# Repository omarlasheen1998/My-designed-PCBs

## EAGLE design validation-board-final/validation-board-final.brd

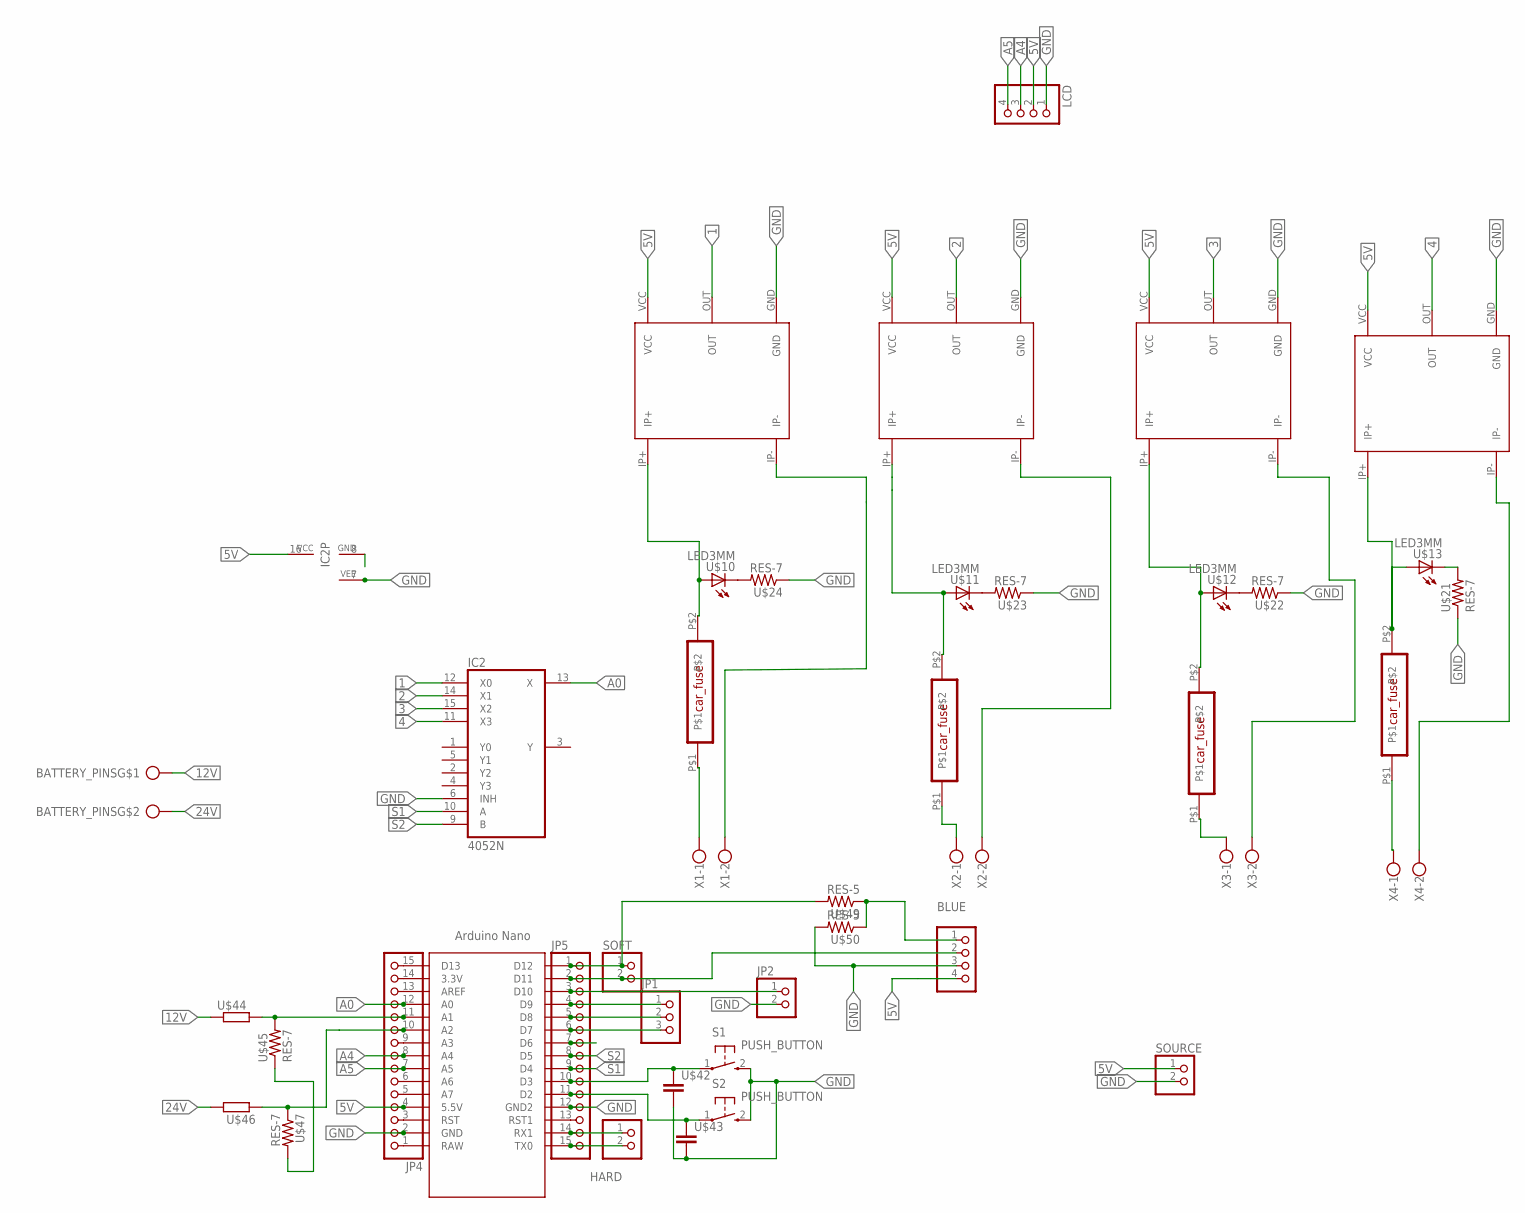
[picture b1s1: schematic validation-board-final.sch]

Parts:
BATTERY_PINS: CON_PTR_2; AK300/2
BLUE: PINHD-4_DATA; 1X04_DATA
HARD: PINHD-2_DATA; 1X02_DATA
IC2: 4052N; DIL16
JP1: PINHD-3_DATA; 1X03_DATA
JP2: PINHD-2_DATA; 1X02_DATA
JP4, JP5: PINHD-1X15; 1X15
LCD: PINHD-4_DATA; 1X04_DATA
S1, S2: PUSH_BUTTON; B3F-10XX
SOFT: PINHD-2_DATA; 1X02_DATA
SOURCE: PINHD-2_DATA; 1X02_DATA
U$1: ARDUINO_NANO; NANO
U$2, U$3, U$4, U$5: CAR_FUSE
U$10, U$11, U$12, U$13: LED3MM
U$21, U$22, U$23, U$24, U$45, U$47: RES-7; 0204/7
U$26, U$27, U$28, U$29: ASC712_MODULE
U$42, U$43: CAPACITOR; C025-025X050
U$44, U$46: R-EU_0207/10; 0207/10
U$49, U$50: RES-5; 0204/5
X1, X2, X3, X4: ROSTA.POWER; W239-302

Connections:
1: IC2.12 (X0), U$26.OUT
2: IC2.14 (X1), U$27.OUT
3: IC2.15 (X2), U$28.OUT
4: IC2.11 (X3), U$29.OUT
5V: BLUE.4, IC2.16 (VCC), JP4.4, LCD.2, SOURCE.1, U$1.5V (5.5V), U$26.VCC, U$27.VCC, U$28.VCC, U$29.VCC
12V: BATTERY_PINS.1, U$44.1
24V: BATTERY_PINS.2, U$46.2
A0: IC2.13 (X), JP4.12, U$1.A0
A4: JP4.8, LCD.3, U$1.A4
A5: JP4.7, LCD.4, U$1.A5
GND: BLUE.3, IC2.6 (INH), IC2.7 (VEE), JP2.2, JP4.2, JP5.12, LCD.1, S1.2 (S), S2.2 (S), SOURCE.2, U$1.GND, U$1.GND1 (GND2), U$21.1, U$22.1, U$23.1, U$24.1, U$26.GND, U$27.GND, U$28.GND, U$29.GND, U$42.2, U$43.2, U$50.2
unnamed: U$13.K (C), U$21.2
unnamed: U$12.K (C), U$22.2
unnamed: U$11.K (C), U$23.2
unnamed: U$10.K (C), U$24.2
unnamed: U$4.P$2, U$12.A, U$28.IP+
unnamed: U$2.P$1, X1.1
unnamed: U$26.IP-, X1.2
unnamed: U$2.P$2, U$10.A, U$26.IP+
unnamed: U$3.P$1, X2.1
unnamed: U$3.P$2, U$11.A, U$27.IP+
unnamed: U$27.IP-, X2.2
unnamed: U$5.P$1, X4.1
unnamed: U$29.IP-, X4.2
unnamed: U$5.P$2, U$13.A, U$29.IP+
unnamed: U$4.P$1, X3.1
unnamed: U$28.IP-, X3.2
unnamed: JP1.1, JP5.4, U$1.D9
unnamed: JP5.10, S1.1, U$1.D3, U$42.1
unnamed: JP4.1, U$1.RAW
unnamed: JP4.3, U$1.RST
unnamed: JP5.11, S2.1, U$1.D2, U$43.1
unnamed: JP1.2, JP5.5, U$1.D8
unnamed: JP1.3, JP5.6, U$1.D7
unnamed: BLUE.2, JP5.2, SOFT.2, U$1.D11
unnamed: JP5.1, SOFT.1, U$1.D12, U$49.2
unnamed: JP2.1, JP5.3, U$1.D10
unnamed: HARD.1, JP5.14, U$1.RX1
unnamed: HARD.2, JP5.15, U$1.TX0
unnamed: JP4.5, U$1.A7
unnamed: JP4.6, U$1.A6
unnamed: JP4.11, U$1.A1, U$44.2, U$45.2
unnamed: U$45.1, U$47.2
unnamed: JP4.10, U$1.A2, U$46.1, U$47.1
unnamed: JP4.9, U$1.A3
unnamed: JP4.13, U$1.AREF
unnamed: JP4.14, U$1.3.3V
unnamed: JP4.15, U$1.D13
unnamed: JP5.13, U$1.RST1
unnamed: BLUE.1, U$49.1, U$50.1
S1: IC2.10 (A), JP5.9, U$1.D4
S2: IC2.9 (B), JP5.8, U$1.D5
S3: JP5.7, U$1.D6

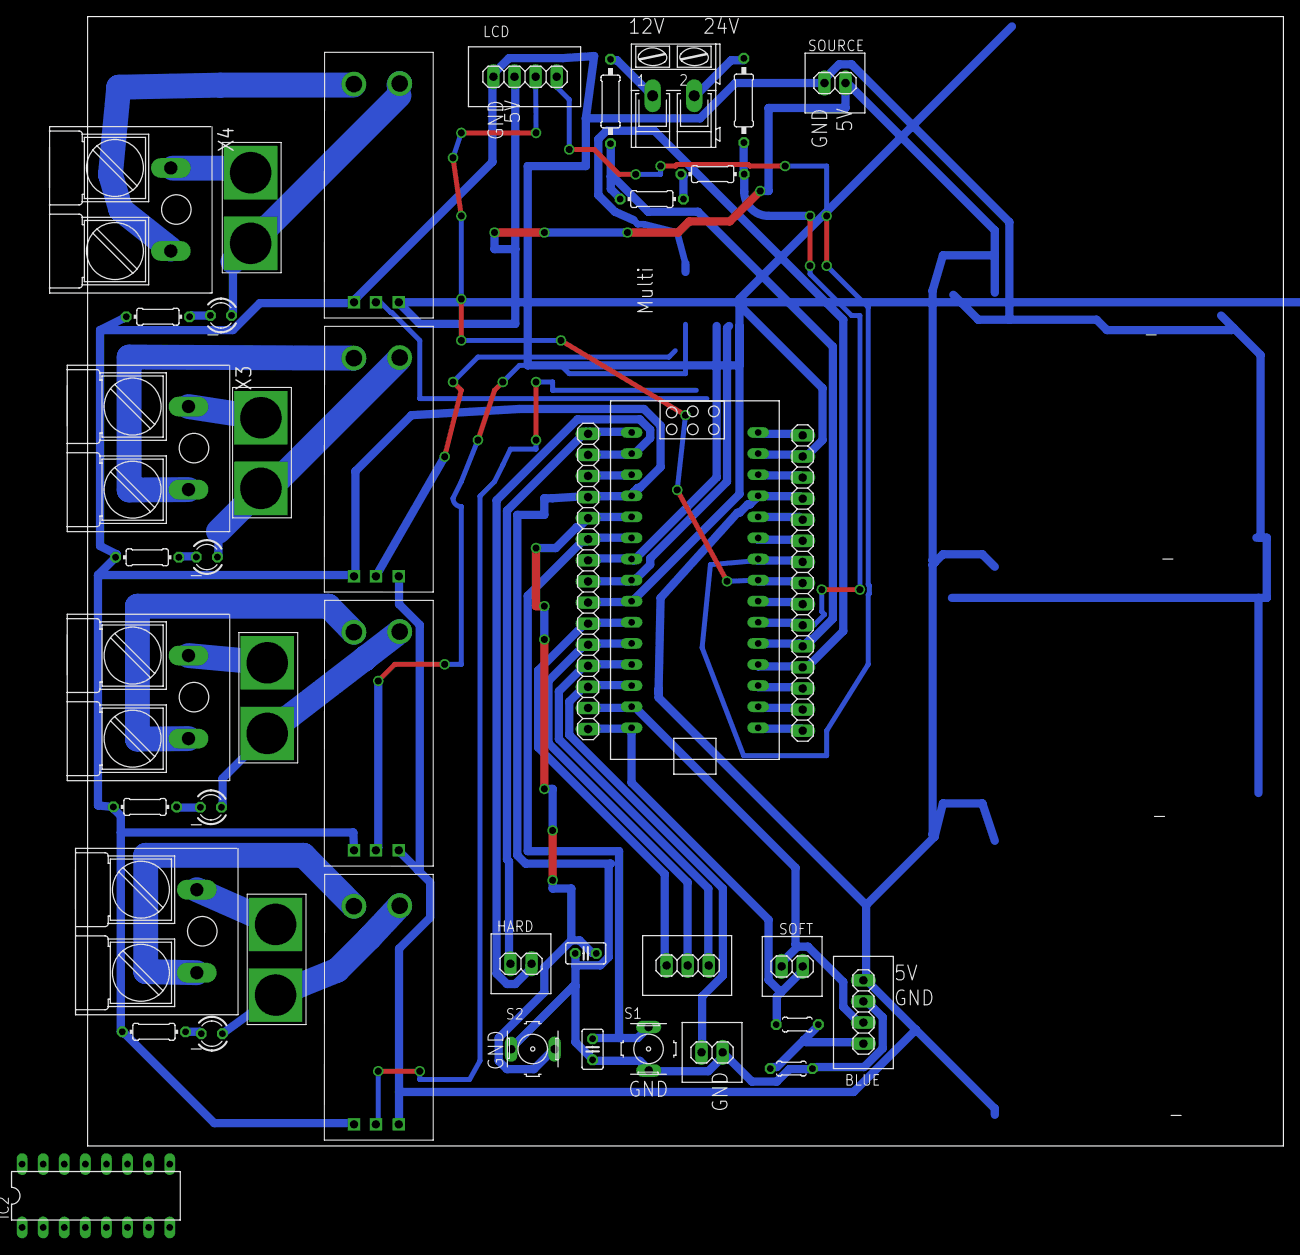
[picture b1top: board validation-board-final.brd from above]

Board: 2 copper layers, 144.0 x 136.0 mm, 42 parts (0 on the bottom side), 53 nets.
